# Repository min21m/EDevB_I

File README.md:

# EDevB_I
My goal was to learn to program Python and Arduino in C++. 
I decided to build a development board using Arduino with flash chips and ADC.

This repository contains all Ki-Cad files and development files for this board.

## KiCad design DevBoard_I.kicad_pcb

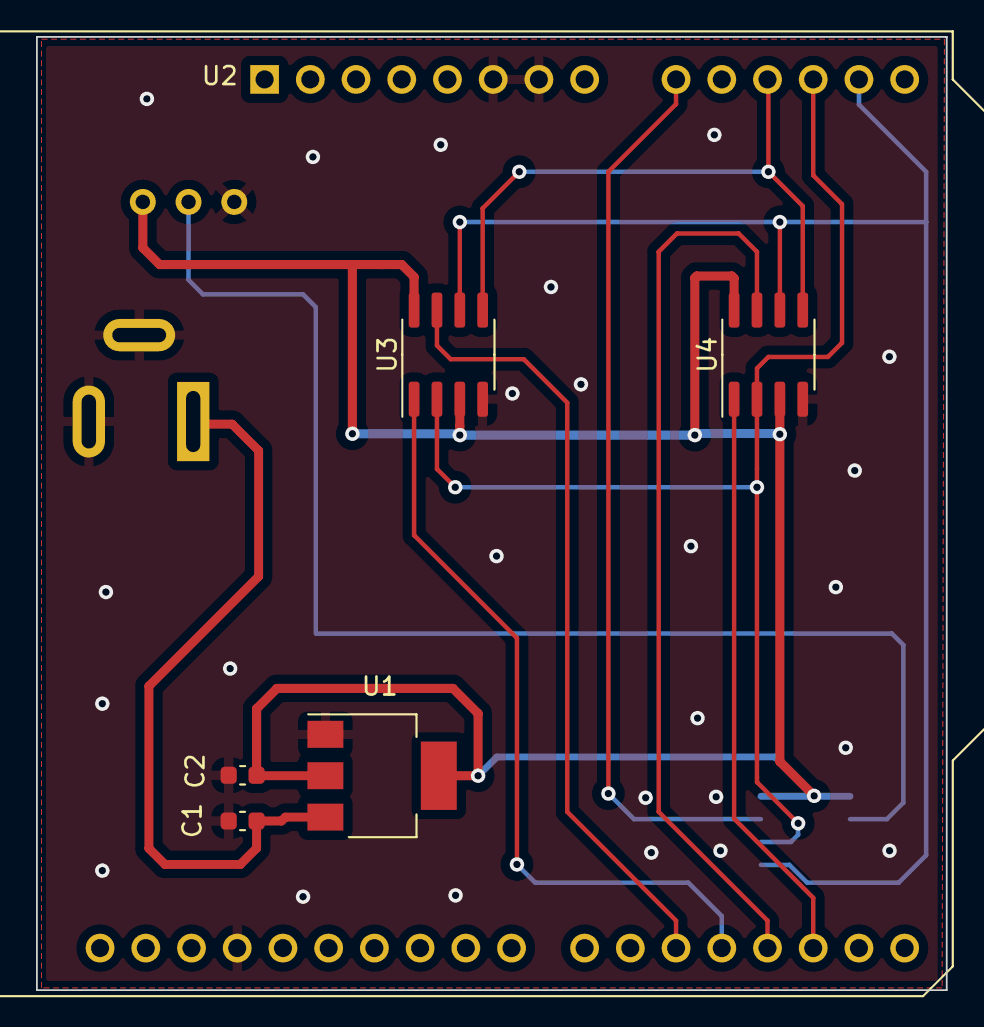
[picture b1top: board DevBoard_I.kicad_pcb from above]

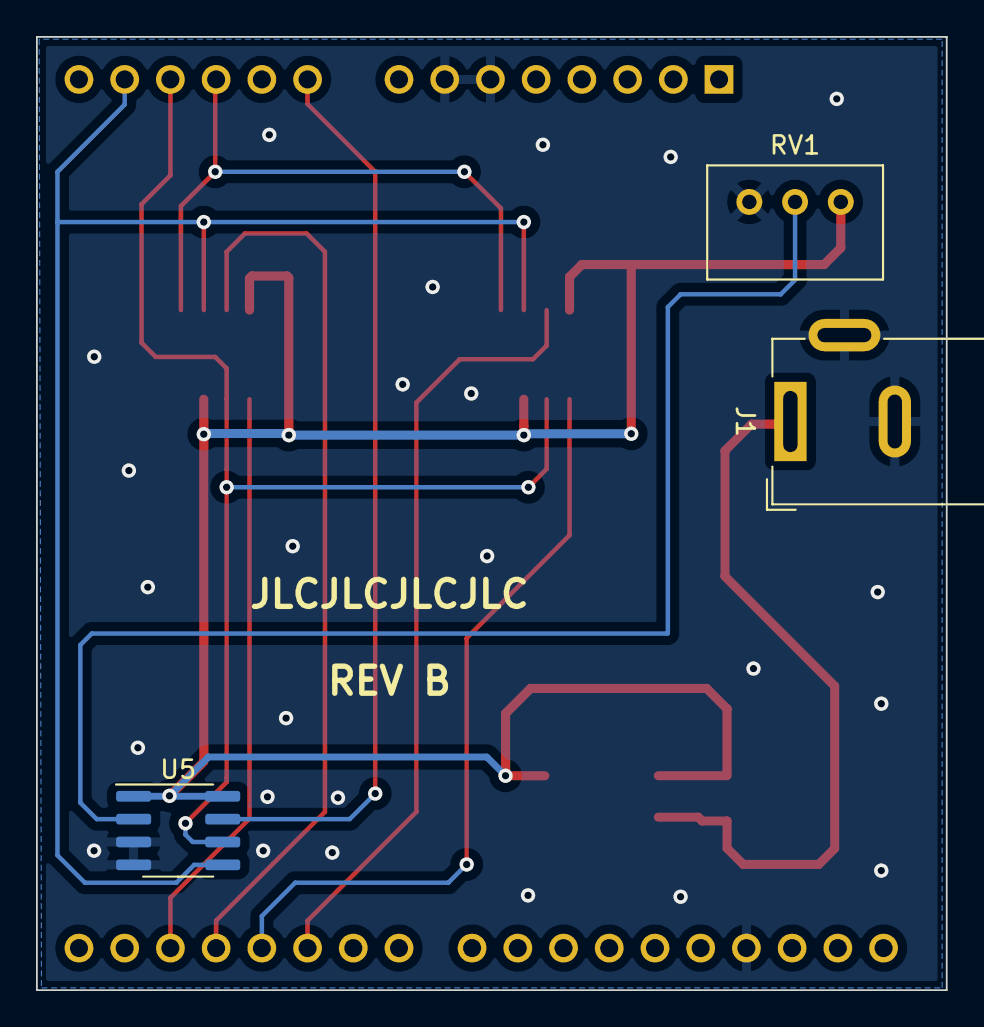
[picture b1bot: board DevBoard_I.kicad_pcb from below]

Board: 2 copper layers, 50.5 x 53.0 mm, 9 parts (3 on the bottom side), 12 nets.

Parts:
C1, C2: C_Polarized_Small_US; C_0603_1608Metric
J1: Barrel_Jack_Switch_Pin3Ring; BarrelJack_Wuerth_6941xx301002
RV1: R_Potentiometer; Potentiometer_Bourns_3299W_Vertical
U1: NCP1117-3.3_SOT223; SOT-223-3_TabPin2
U2: Arduino_UNO_R3
U3, U4: AT25SF081-SSHD-X; SOIC-8_3.9x4.9mm_P1.27mm
U5: MCP3550-60-ESN; SOIC-8_3.9x4.9mm_P1.27mm

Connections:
/MISO: U2.12 (A3), U3.2 (SO/IO1), U4.2 (SO/IO1), U5.6 (SDO/~RDY)
/MOSI: U2.11 (A2), U3.5 (SI/IO0), U4.5 (SI/IO0)
/SCK: U2.13 (SDA/A4), U3.6 (SCK), U4.6 (SCK), U5.5 (SCK)
GND: C1.2, C2.2, J1.2, J1.3, RV1.3, U1.1 (GND), U2.6 (GND), U2.7 (GND), U2.29 (GND), U3.4 (GND), U4.4 (GND), U5.3 (Vin-), U5.4 (VSS)
unnamed: C1.1, J1.1, U1.3 (VI)
unnamed: C2.1, RV1.1, U1.2 (VO), U3.3 (~WP/IO2), U3.8 (VCC), U4.3 (~WP/IO2), U4.8 (VCC), U5.1 (Vref), U5.8 (VDD)
unnamed: RV1.2, U5.2 (Vin+)
unnamed: U2.9 (A0), U5.7 (~CS)
unnamed: U2.17 (D2), U4.1 (~CS)
unnamed: U2.18 (D3), U4.7 (~HOLD/IO3)
unnamed: U2.19 (D4), U3.1 (~CS)
unnamed: U2.20 (D5), U3.7 (~HOLD/IO3)

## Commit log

2023-04-01 Initial Commit
    Designing and developing a circuit board for practicing Python and Arduino programming.
2023-04-01 Update .gitignore
    gitignore all zip files and fp-info-cache file from KiCad
2023-04-01 gitignore KiCad project file
    Ignore constantly changing KiCad project file
2023-04-01 Add Company Name to schematic
2023-04-01 Update DevBoard_I.kicad_sch
    Change capitalization of the company name
2023-04-01 Delete DevBoard_I.kicad_pro
    Project file is constantly changing and it doesn't need to be tracked.
2023-04-01 Create Cats and Dogs.txt
    This will be deleted later..
2023-04-01 Update Cats and Dogs.txt
    Add 50 cats to our new world
2023-04-01 Update Cats and Dogs.txt
    Add 85 Dogs and kill some cats
2023-04-01 Revert "Delete DevBoard_I.kicad_pro"
    This reverts commit 8bd720d51dcf6f32c03162aecf4950a8cf32558a.
2023-04-01 Revert "Revert "Delete DevBoard_I.kicad_pro""
    This reverts commit c9bbd82a328cd08e5941fcc48a5683c8b9f6eb81.
2023-04-01 Create Lizards and Alligators.txt
    Add 37 Lizards
2023-05-06 Rev_A Update
    U5 footprint change.
    Moved J1 and RV1 to the bottom.
    Re-route accordingly.
2023-06-10 Replaced missing .pro file.
2023-06-10 Added MCP3350 datasheet
